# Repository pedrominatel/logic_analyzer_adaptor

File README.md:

# Generic Saleae 24Mhz 8Ch Logical Analyzer Adaptor

Generic Locical Analyzer adaptor for wireup soldering

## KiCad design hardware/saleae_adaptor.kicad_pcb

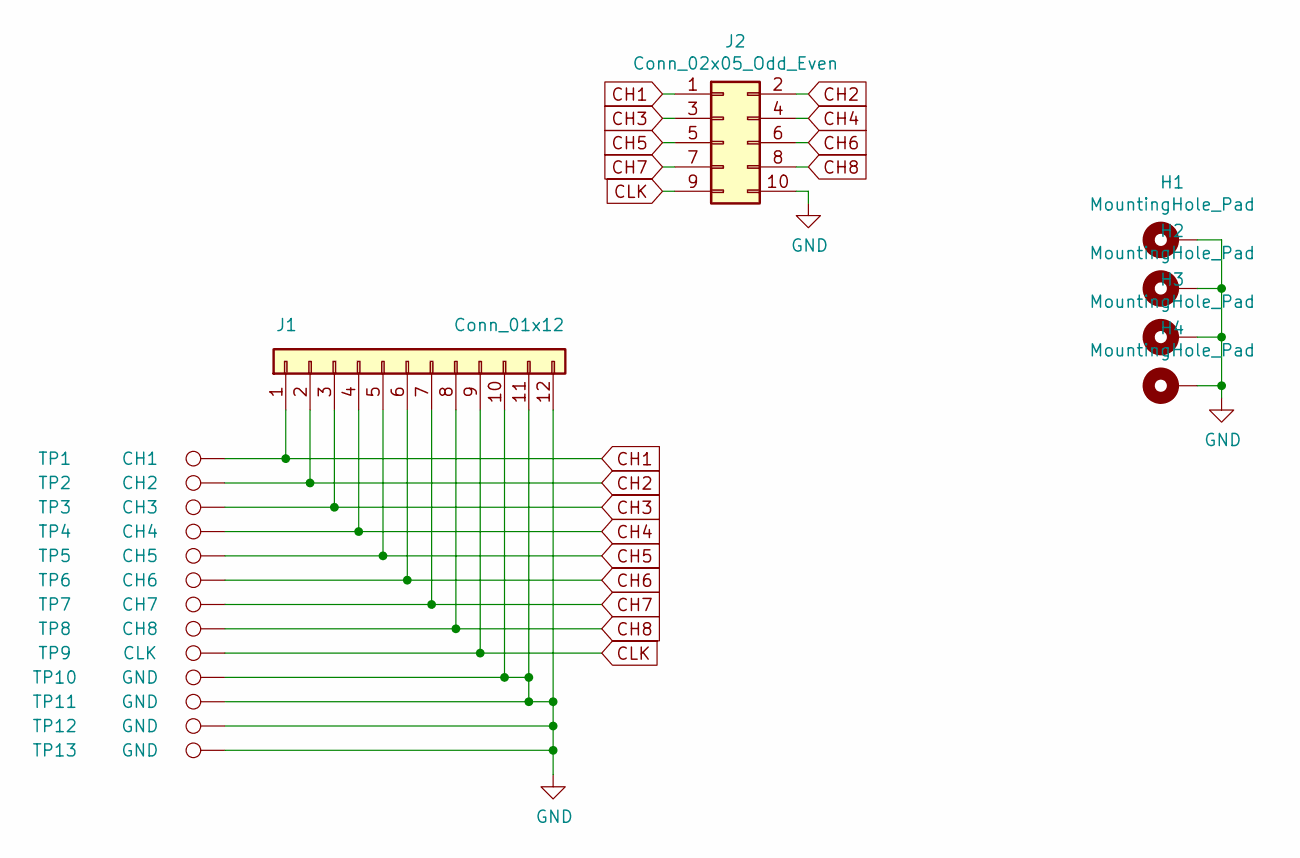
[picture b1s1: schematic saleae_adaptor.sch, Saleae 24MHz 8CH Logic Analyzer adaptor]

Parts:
H1, H2, H3, H4: MountingHole_Pad; MountingHole_2.5mm_Pad_Via
J1: Conn_01x12; PinHeader_1x12_P2.54mm_Vertical
J2: Conn_02x05_Odd_Even; PinSocket_2x05_P2.54mm_Horizontal
TP1: CH1; TestPoint_Pad_D4.0mm
TP2: CH2; TestPoint_Pad_D4.0mm
TP3: CH3; TestPoint_Pad_D4.0mm
TP4: CH4; TestPoint_Pad_D4.0mm
TP5: CH5; TestPoint_Pad_D4.0mm
TP6: CH6; TestPoint_Pad_D4.0mm
TP7: CH7; TestPoint_Pad_D4.0mm
TP8: CH8; TestPoint_Pad_D4.0mm
TP9: CLK; TestPoint_Pad_D4.0mm
TP10, TP11, TP12, TP13: GND; TestPoint_Pad_4.0x4.0mm

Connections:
CH1: J1.1, J2.1, TP1.1
CH2: J1.2, J2.2, TP2.1
CH3: J1.3, J2.3, TP3.1
CH4: J1.4, J2.4, TP4.1
CH5: J1.5, J2.5, TP5.1
CH6: J1.6, J2.6, TP6.1
CH7: J1.7, J2.7, TP7.1
CH8: J1.8, J2.8, TP8.1
CLK: J1.9, J2.9, TP9.1
GND: H1.1, H2.1, H3.1, H4.1, J1.10, J1.11, J1.12, J2.10, TP10.1, TP11.1, TP12.1, TP13.1

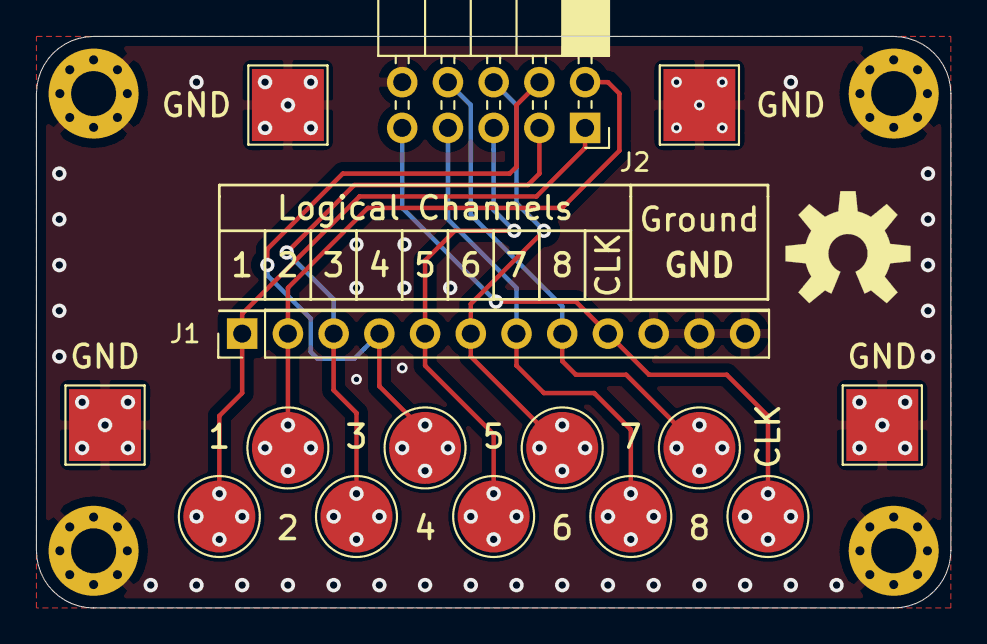
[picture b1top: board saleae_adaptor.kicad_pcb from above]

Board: 2 copper layers, 50.8 x 31.8 mm, 19 parts (0 on the bottom side), 10 nets.

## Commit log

2020-10-24 Project added
2020-10-24 Added 3D asset folder and file
2020-10-24 Added 3D file
2020-10-24 Added new GND pad
